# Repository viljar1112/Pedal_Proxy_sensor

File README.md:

Pedal - analog output
========================

  * This is a foot pedal project that use QRE1113 IR sensor.
  * Outputs 0-5V range analog signal (but can be used with 3,3V).
  * Pedal has relatively low profile and NO extruding parts outside of it's footprint (like gear rack).
  * I used it for children electric car's gas pedal

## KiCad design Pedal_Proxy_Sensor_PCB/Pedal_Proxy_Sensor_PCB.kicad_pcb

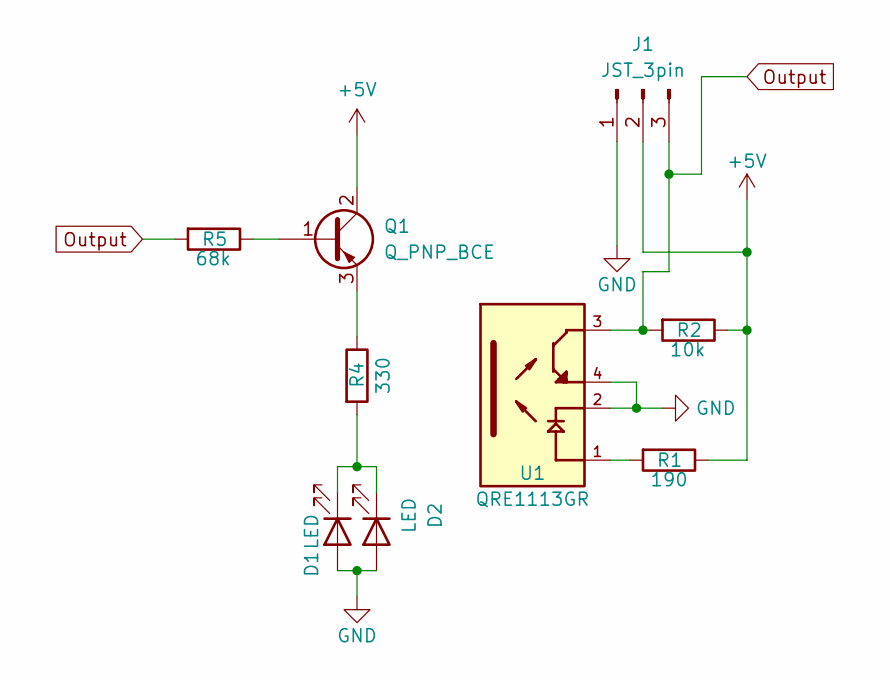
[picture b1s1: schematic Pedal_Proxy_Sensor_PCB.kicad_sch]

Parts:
D1: LED; LED_0805_2012Metric_Pad1.15x1.40mm_HandSolder
D2: LED; LED_D5.0mm_Horizontal_O3.81mm_Z3.0mm
J1: JST_3pin; JST_XH_B3B-XH-A_1x03_P2.50mm_Vertical_Mod
Q1: Q_PNP_BCE; SOT-23_Handsoldering
R1: 190; R_0603_1608Metric_Pad0.98x0.95mm_HandSolder
R2: 10k; R_0603_1608Metric_Pad0.98x0.95mm_HandSolder
R4: 330; R_0805_2012Metric_Pad1.20x1.40mm_HandSolder
R5: 68k; R_0603_1608Metric_Pad0.98x0.95mm_HandSolder
U1: QRE1113GR

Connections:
+5V: J1.2, Q1.2 (C), R1.1, R2.1
GND: D1.2 (A), D2.2 (A), J1.1, U1.2, U1.4
unnamed: D1.1 (K), D2.1 (K), R4.2
unnamed: Q1.1 (B), R5.1
unnamed: Q1.3 (E), R4.1
unnamed: R1.2, U1.1
Output: J1.3, R2.2, R5.2, U1.3

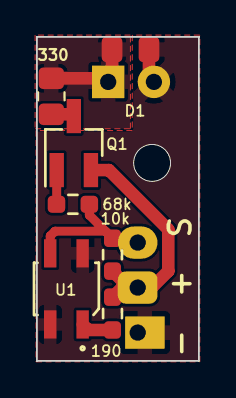
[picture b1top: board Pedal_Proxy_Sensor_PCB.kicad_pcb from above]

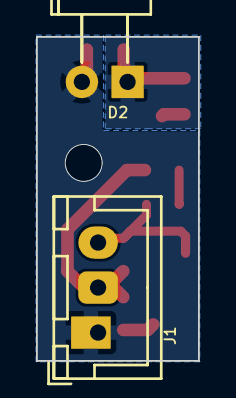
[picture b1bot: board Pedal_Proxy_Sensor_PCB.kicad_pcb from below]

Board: 2 copper layers, 9.0 x 18.0 mm, 9 parts (2 on the bottom side), 7 nets.
